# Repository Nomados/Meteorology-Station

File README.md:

# Meteorology-Station
This device is based on stm32F051 MCU and features measurements of 
temperature, humidity and pressure. It uses sh1106 1.3 OLED display to 
show data and is capable to transfer data via two UARTs if you want to 
organize radio communication. It also has Eagle PCB layout and ready to 
use gerbers (SeedStudio format).

This application uses Chibios/RT RTOS (2.6.x) and uGFX graphics engine.
You should download this software. Place Chibios and uGFX in ../ folder 
of makefile's location. 

For more details please visit:
http://mcudu.blogspot.kr/2015/11/meteorology-station.html

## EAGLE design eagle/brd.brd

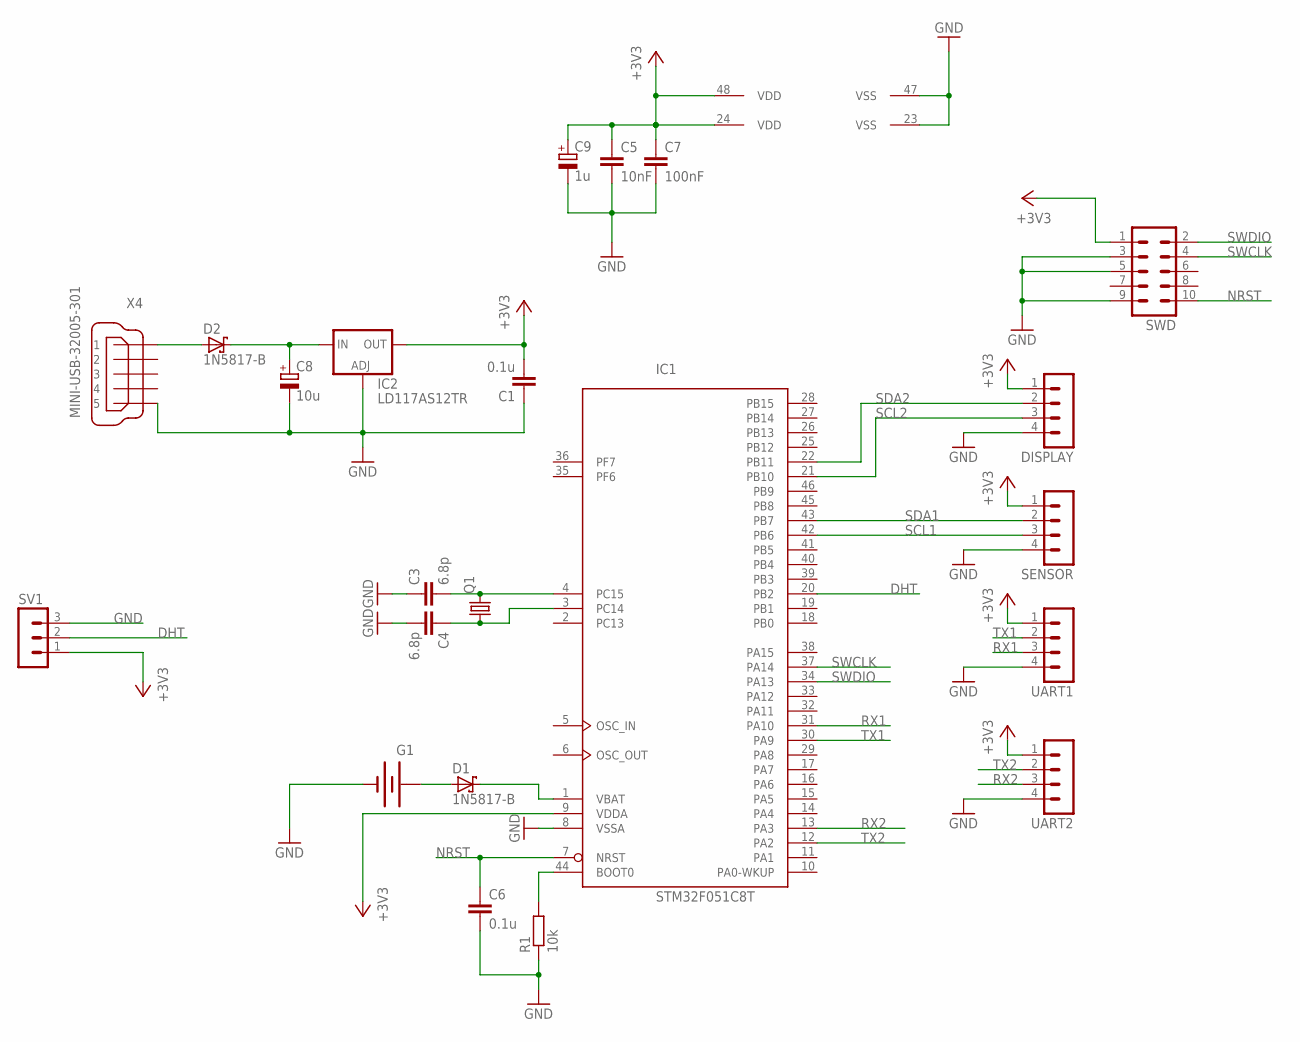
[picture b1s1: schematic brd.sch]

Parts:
C1: 0.1u; C025-024X044
C3, C4: 6.8p; C0805
C5: 10nF; C0805
C6: 0.1u; C0805
C7: 100nF; C0805
C8: 10u; E2,5-6E
C9: 1u; E2,5-6E
D1, D2: 1N5817-B; DO41-7.6
DISPLAY: MA04-1
G1: BATTERY20PTH; BATTCOM_20MM_PTH
IC1: STM32F051C8T; LQFP48
IC2: LD117AS12TR; SOT223
Q1: CRYSTALTC26H; TC26H
R1: 10k; R0805
SENSOR: MA04-1
SV1: MA03-1
SWD: MA05-2
UART1, UART2: MA04-1
X4: MINI-USB-32005-301; 32005-301

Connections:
+3V3: C1.2, C5.1, C7.1, C9.+, DISPLAY.1, IC1.9 (VDDA), IC1.24 (VDD), IC1.48 (VDD), IC2.4 (OUT), SENSOR.1, SV1.1, SWD.1, UART1.1, UART2.1
DHT: IC1.20 (PB2), SV1.2
GND: C1.1, C3.1, C4.2, C5.2, C6.2, C7.2, C8.-, C9.-, DISPLAY.4, G1.2 (-), IC1.8 (VSSA), IC1.23 (VSS), IC1.47 (VSS), IC2.1 (ADJ), R1.1, SENSOR.4, SV1.3, SWD.3, SWD.5, SWD.9, UART1.4, UART2.4, X4.5
unnamed: C8.+, D2.C, IC2.3 (IN)
unnamed: C3.2, IC1.4 (PC15), Q1.2
unnamed: IC1.44 (BOOT0), R1.2
unnamed: C4.1, IC1.3 (PC14), Q1.1
unnamed: D2.A, X4.1
unnamed: D1.C, IC1.1 (VBAT)
unnamed: D1.A, G1.1 (+)
NRST: C6.1, IC1.7 (NRST), SWD.10
RX1: IC1.31 (PA10), UART1.3
RX2: IC1.13 (PA3), UART2.3
SCL1: IC1.42 (PB6), SENSOR.3
SCL2: DISPLAY.3, IC1.21 (PB10)
SDA1: IC1.43 (PB7), SENSOR.2
SDA2: DISPLAY.2, IC1.22 (PB11)
SWCLK: IC1.37 (PA14), SWD.4
SWDIO: IC1.34 (PA13), SWD.2
TX1: IC1.30 (PA9), UART1.2
TX2: IC1.12 (PA2), UART2.2

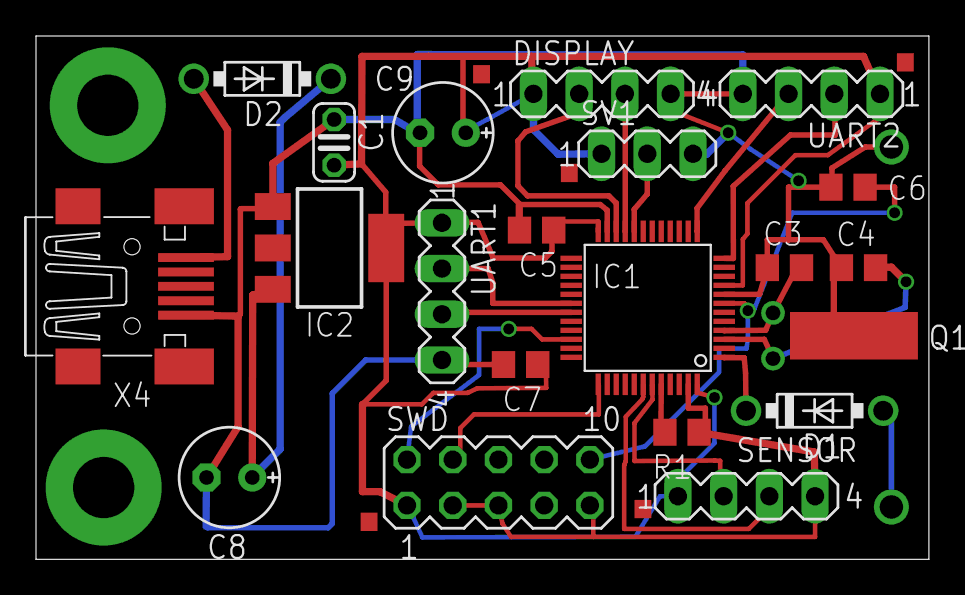
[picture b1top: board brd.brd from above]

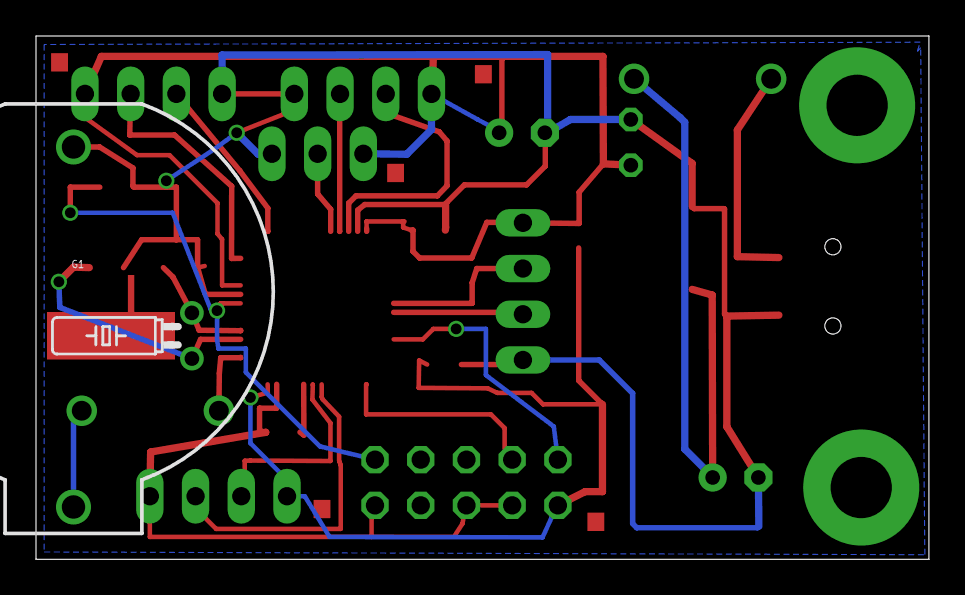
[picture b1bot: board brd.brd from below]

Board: 2 copper layers, 49.6 x 29.1 mm, 22 parts (2 on the bottom side), 21 nets.

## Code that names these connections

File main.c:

/*
    ChibiOS/RT - Copyright (C) 2006-2013 Giovanni Di Sirio

    Licensed under the Apache License, Version 2.0 (the "License");
    you may not use this file except in compliance with the License.
    You may obtain a copy of the License at

        http://www.apache.org/licenses/LICENSE-2.0

    Unless required by applicable law or agreed to in writing, software
    distributed under the License is distributed on an "AS IS" BASIS,
    WITHOUT WARRANTIES OR CONDITIONS OF ANY KIND, either express or implied.
    See the License for the specific language governing permissions and
    limitations under the License.
 */

#include "ch.h"
#include "hal.h"
#include "gfx.h"
#include "BarometerData.h"
#include "dht11.h"
#include <string.h>
#include "chprintf.h"




BaroData bd; // baro data structure
static uint8_t dht_buffer[5]; // DHT buffer


I2CConfig i2cconfig =
{
		0x00901D2B,
		0,
		0
};



SerialConfig sc =
{
		19200,
		0,
		0,
		0

};



/* itoa: */
void itoa(int n, char s[])
{

	/* reverse the string */
	void reverse(char s[])
	{
		int i, j;
		char c;

		for (i = 0, j = strlen(s)-1; i<j; i++, j--) {
			c = s[i];
			s[i] = s[j];
			s[j] = c;
		}
	}

	int i, sign;

	if ((sign = n) < 0)
		n = -n;
	i = 0;
	do {
		s[i++] = n % 10 + '0';
	} while ((n /= 10) > 0);
	if (sign < 0)
		s[i++] = '-';
	s[i] = '\0';
	reverse(s);
}





/*
 * OLED thread, times are in milliseconds.
 */
static WORKING_AREA(waOLED, 512);
static msg_t Oled(void *arg)
{
	(void)arg;
	chRegSetThreadName("oled");


	gfxInit();
	font_t font = gdispOpenFont("UI1");
	font_t font1 = gdispOpenFont("UI2");
	gdispSetClip(0, 0, gdispGetWidth(), gdispGetHeight());
	uint8_t x = 7, y = 15;

	while (true)
	{
		char ch[10];
		int temperature = 0;
		int pressure = 0;
		readBarometerData(&bd, 1);
		temperature = (int)bd.TEMP;
		pressure = (int)(bd.PRESSURE * 0.0075);
		int alt = (int)getAltitude(&bd);

		gdispClear(Black);


		gdispDrawString(x, y - 12, "Weather ", font1, White);

		gdispDrawString(x, y, "temperature: ", font, White);
		gdispDrawString(x, y + 12, "pressure: ", font, White);
		gdispDrawString(x, y + 24, "altitude: ", font, White);
		gdispDrawString(x, y + 36, "humidity: ", font, White);



		itoa(temperature, ch);
		gdispDrawString(x+80, y, ch, font, White);

		itoa(pressure, ch);
		gdispDrawString(x+80, y+12, ch, font, White);

		itoa(alt, ch);
		gdispDrawString(x+80, y+24, ch, font, White);



		if (read_DHT11(&dht_buffer[0]) == DHT11_OK)
		{
			itoa(dht_buffer[0], ch);
			gdispDrawString(x+80, y+36, ch, font, White);
			chprintf((BaseSequentialStream*)&SD2, "Temperature: %02dC  pressure: %d kPA  humidity: %02d %%\n\r", temperature, pressure/100, dht_buffer[0]);
		}
		else
		{
			gdispDrawString(x+80, y+36, "Err", font, White);
			chprintf((BaseSequentialStream*)&SD2, "Temperature: %02dC  pressure=%dkPA can't read DHT11 sensor\n\r", temperature, pressure/100);
		}




		gdispGFlush(gdispGetDisplay(0));
		chThdSleepMilliseconds(1000);
	}

	return 0;

}



/*
 * Application entry point.
 */
int main(void)
{
	/*
	 * System initializations.
	 * - HAL initialization, this also initializes the configured device drivers
	 *   and performs the board-specific initializations.
	 * - Kernel initialization, the main() function becomes a thread and the
	 *   RTOS is active.
	 */
	halInit();
	chSysInit();


	/*
	 * Starting the I2C driver 2 for bmp180.
	 */
	i2cStart(&I2CD2, &i2cconfig);
	initialize_bmp180(&bd, 3);
	/*
	 * Activates the serial driver 1 using the driver default configuration.
	 * PA9 and PA10 are routed to USART1 and PA2 and PA3 to USART2
	 */
	sdStart(&SD1, &sc);
	sdStart(&SD2, &sc);

	/*
	 * Creates the threads.
	 */
	//chThdCreateStatic(waDHT11, sizeof(waDHT11), NORMALPRIO - 4, DHT11_Reader, NULL);
	chThdCreateStatic(waOLED, sizeof(waOLED), NORMALPRIO + 1, Oled, NULL);


	while (TRUE)
	{
		chThdSleepMilliseconds(1000);
	}
}

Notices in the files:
parts and their libraries:
SparkFun-Electromechanical: Licensing: Creative Commons ShareAlike 4.0 International - https://creativecommons.org/licenses/by-sa/4.0
